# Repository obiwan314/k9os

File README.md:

k9os
====

A collection of software to control a Raspberry PI based K9 robot.

This is a hardware/software project in progress that is documented on my blog at http://gwfrontiers.blogspot.com.

This project is intended to be checked out on your raspberry pi.
Once this is done run:

cd bin
sudo ./install.sh

This will install the Arduino scripts into the required locations and install and configure the k9os daemon for interfacing over USB to the two arduinos used to control the robot.

This is a personal research project and any sourcecode or hardware designs are provided here without any warrenty or gaurentee.

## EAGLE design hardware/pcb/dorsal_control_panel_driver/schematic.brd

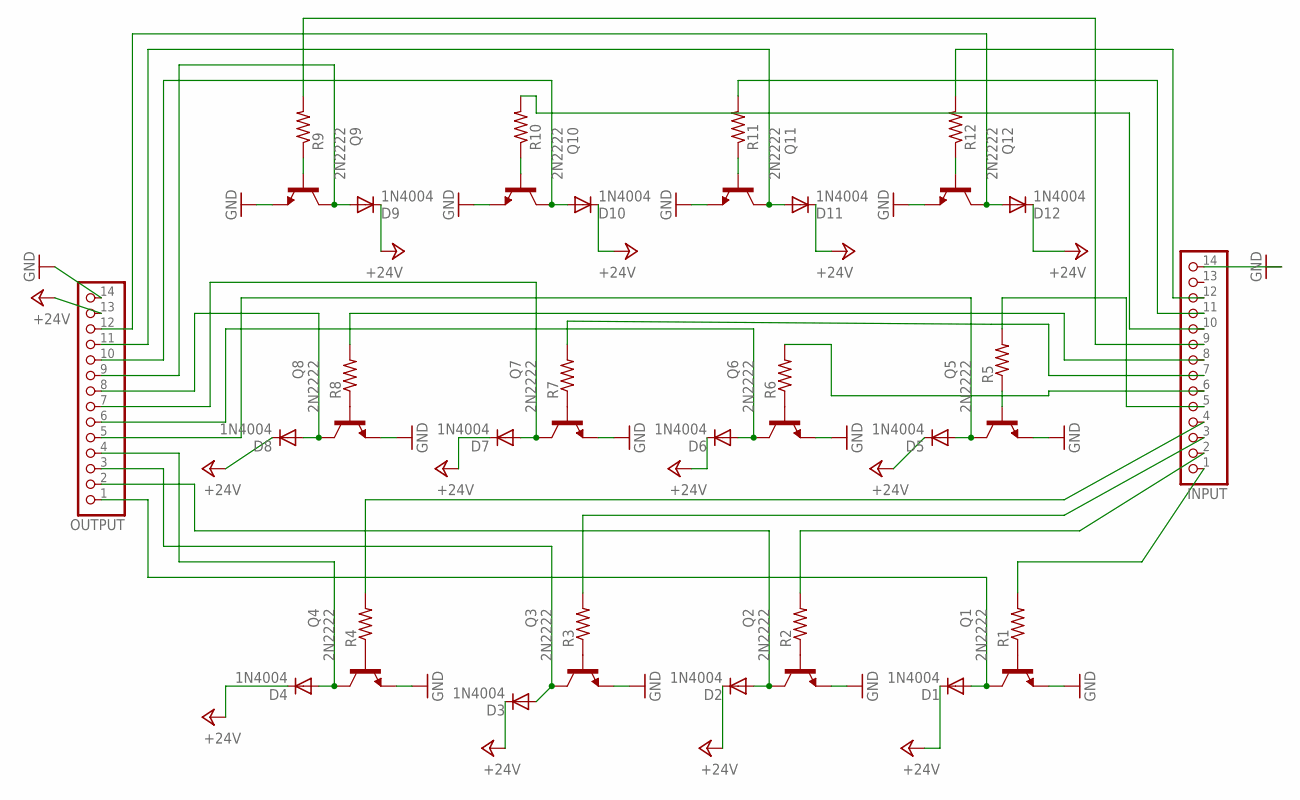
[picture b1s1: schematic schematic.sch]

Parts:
D1, D2, D3, D4, D5, D6, D7, D8, D9, D10, D11, D12: 1N4004; DO41-10; MPN 1N4004
INPUT: PINHD-1X14; 1X14
OUTPUT: PINHD-1X14; 1X14
Q1, Q2, Q3, Q4, Q5, Q6, Q7, Q8, Q9, Q10, Q11, Q12: 2N2222; TO92-EBC-OVAL; MPN PN2222ATF
R1, R2, R3, R4, R5, R6, R7, R8, R9, R10, R11, R12: R-US_0309/12; 0309/12

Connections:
+24V: D1.C, D2.C, D3.C, D4.C, D5.C, D6.C, D7.C, D8.C, D9.C, D10.C, D11.C, D12.C, OUTPUT.13
GND: INPUT.14, OUTPUT.14, Q1.E, Q2.E, Q3.E, Q4.E, Q5.E, Q6.E, Q7.E, Q8.E, Q9.E, Q10.E, Q11.E, Q12.E
unnamed: D1.A, OUTPUT.1, Q1.C
unnamed: Q1.B, R1.1
unnamed: INPUT.1, R1.2
unnamed: D2.A, OUTPUT.2, Q2.C
unnamed: Q2.B, R2.1
unnamed: INPUT.2, R2.2
unnamed: D3.A, OUTPUT.3, Q3.C
unnamed: Q3.B, R3.1
unnamed: INPUT.3, R3.2
unnamed: D4.A, OUTPUT.4, Q4.C
unnamed: Q4.B, R4.1
unnamed: INPUT.4, R4.2
unnamed: D5.A, OUTPUT.5, Q5.C
unnamed: Q5.B, R5.1
unnamed: INPUT.5, R5.2
unnamed: D6.A, OUTPUT.6, Q6.C
unnamed: Q6.B, R6.1
unnamed: INPUT.6, R6.2
unnamed: D7.A, OUTPUT.7, Q7.C
unnamed: Q7.B, R7.1
unnamed: INPUT.7, R7.2
unnamed: D8.A, OUTPUT.8, Q8.C
unnamed: Q8.B, R8.1
unnamed: INPUT.8, R8.2
unnamed: D9.A, OUTPUT.9, Q9.C
unnamed: Q9.B, R9.1
unnamed: INPUT.9, R9.2
unnamed: D10.A, OUTPUT.10, Q10.C
unnamed: Q10.B, R10.1
unnamed: INPUT.10, R10.2
unnamed: D11.A, OUTPUT.11, Q11.C
unnamed: Q11.B, R11.1
unnamed: INPUT.11, R11.2
unnamed: D12.A, OUTPUT.12, Q12.C
unnamed: Q12.B, R12.1
unnamed: INPUT.12, R12.2

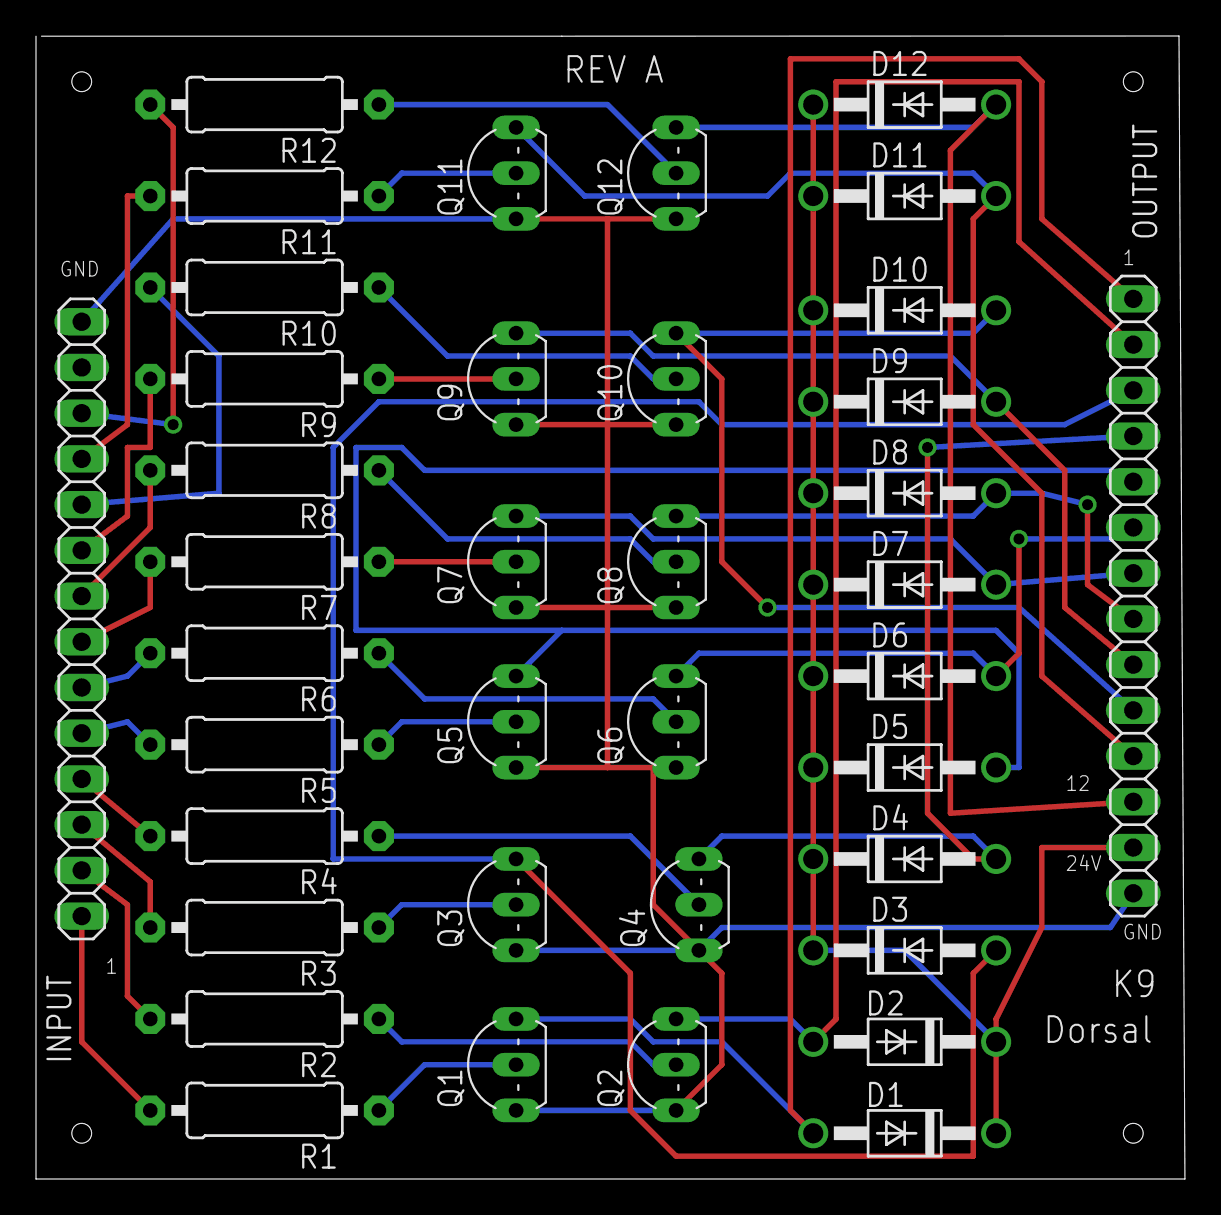
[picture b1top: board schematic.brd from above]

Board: 2 copper layers, 63.8 x 63.5 mm, 38 parts (0 on the bottom side), 38 nets.

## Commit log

2014-03-18 Moved from previous git project
2014-03-18 Add bin directory
2014-03-18 Updated install script with daemon install
2014-03-18 Added documentation, drawings and simulations
2014-03-29 Added Eagle PCB files
2014-03-29 Moved PCB layout files into their own folder
2014-04-06 Drive now operates all motors, the ultrasonic sensor and the compass
2014-04-06 Added a script to monitor a serial port from the PI
2014-04-06 JSON support for moving and turning
2014-04-06 Debugging- sketch now runs motor continuosly
2014-04-07 Added support for Raspberry PI remote control.
2014-04-08 Added turn in place feature for remote control. Disabled turn while moving (bias) as it was hard to control from the remote.
2014-04-08 Added motor wiring diagram
2014-04-12 Start of web server support
2014-04-13 drive commands and rpc access in progress
2014-04-15 Minor changes for remote serial streaming
2014-04-15 RPC Server is now working
2014-04-15 Now have remote rotation working
2014-04-15 Adding raw web template
2014-04-15 Basic web controls work now.
2014-04-17 Playing sounds works
2014-04-19 Moved sound playing functionallity to the control panel server from the RPC server
2014-05-16 Increased baud rate.
2014-05-16 Rebuilding daemon
2014-05-16 Added two separate serial monitors
2014-05-16 Added new library
2014-07-11 Changes made directly on the PI
2014-07-11 Deleted library docs
2014-07-12 Installed tail servos and added support to trigger them.
2014-07-14 Multiple changes. Tail now wags when triggered.
2014-07-25 Overdue for a check in. Web interface now contains multiple enhancements.
2014-07-27 Added control of LCD panel to web UI.
2014-09-23 Printer support
